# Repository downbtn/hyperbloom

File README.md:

# hyperbloom
great value chipwhisperer

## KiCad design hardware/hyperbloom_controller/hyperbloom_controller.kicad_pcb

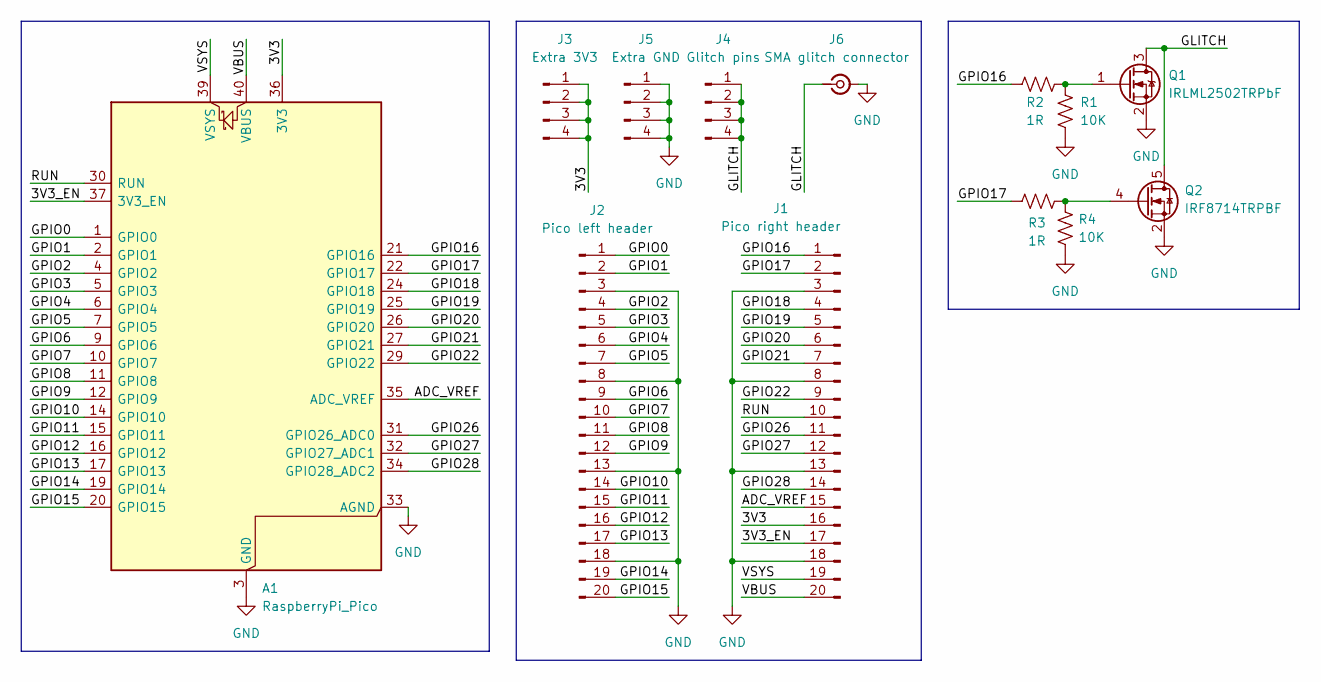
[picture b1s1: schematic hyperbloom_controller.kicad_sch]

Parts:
A1: RaspberryPi_Pico; RaspberryPi_Pico_Common_Unspecified
J1: Pico right header; PinHeader_1x20_P2.54mm_Vertical
J2: Pico left header; PinHeader_1x20_P2.54mm_Vertical
J3: Extra 3V3; PinHeader_1x04_P2.54mm_Vertical
J4: Glitch pins; PinHeader_1x04_P2.54mm_Vertical
J5: Extra GND; PinHeader_1x04_P2.54mm_Vertical
J6: SMA glitch connector; SMA_Amphenol_901-144_Vertical
Q1: IRLML2502TRPbF; SOT-23
Q2: IRF8714TRPBF; SOIC-8_3.9x4.9mm_P1.27mm
R1, R4: 10K; R_0805_2012Metric_Pad1.20x1.40mm_HandSolder
R2, R3: 1R; R_0805_2012Metric_Pad1.20x1.40mm_HandSolder

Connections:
/3V3: A1.36 (3V3), J1.16, J3.1, J3.2, J3.3, J3.4
/3V3_EN: A1.37 (3V3_EN), J1.17
/ADC_VREF: A1.35 (ADC_VREF), J1.15
/GLITCH: J4.1, J4.2, J4.3, J4.4, J6.1 (In), Q1.3 (D), Q2.5 (D), Q2.6 (D), Q2.7 (D), Q2.8 (D)
/GPIO0: A1.1 (GPIO0), J2.1
/GPIO1: A1.2 (GPIO1), J2.2
/GPIO2: A1.4 (GPIO2), J2.4
/GPIO3: A1.5 (GPIO3), J2.5
/GPIO4: A1.6 (GPIO4), J2.6
/GPIO5: A1.7 (GPIO5), J2.7
/GPIO6: A1.9 (GPIO6), J2.9
/GPIO7: A1.10 (GPIO7), J2.10
/GPIO8: A1.11 (GPIO8), J2.11
/GPIO9: A1.12 (GPIO9), J2.12
/GPIO10: A1.14 (GPIO10), J2.14
/GPIO11: A1.15 (GPIO11), J2.15
/GPIO12: A1.16 (GPIO12), J2.16
/GPIO13: A1.17 (GPIO13), J2.17
/GPIO14: A1.19 (GPIO14), J2.19
/GPIO15: A1.20 (GPIO15), J2.20
/GPIO16: A1.21 (GPIO16), J1.1, R2.1
/GPIO17: A1.22 (GPIO17), J1.2, R3.1
/GPIO18: A1.24 (GPIO18), J1.4
/GPIO19: A1.25 (GPIO19), J1.5
/GPIO20: A1.26 (GPIO20), J1.6
/GPIO21: A1.27 (GPIO21), J1.7
/GPIO22: A1.29 (GPIO22), J1.9
/GPIO26: A1.31 (GPIO26_ADC0), J1.11
/GPIO27: A1.32 (GPIO27_ADC1), J1.12
/GPIO28: A1.34 (GPIO28_ADC2), J1.14
/RUN: A1.30 (RUN), J1.10
/VBUS: A1.40 (VBUS), J1.20
/VSYS: A1.39 (VSYS), J1.19
GND: A1.3 (GND), A1.8 (GND), A1.13 (GND), A1.18 (GND), A1.23 (GND), A1.28 (GND), A1.33 (AGND), A1.38 (GND), J1.3, J1.8, J1.13, J1.18, J2.3, J2.8, J2.13, J2.18, J5.1, J5.2, J5.3, J5.4, J6.2 (Ext), Q1.2 (S), Q2.1 (S), Q2.2 (S), Q2.3 (S), R1.2, R4.2
unnamed: Q1.1 (G), R1.1, R2.2
unnamed: Q2.4 (G), R3.2, R4.1

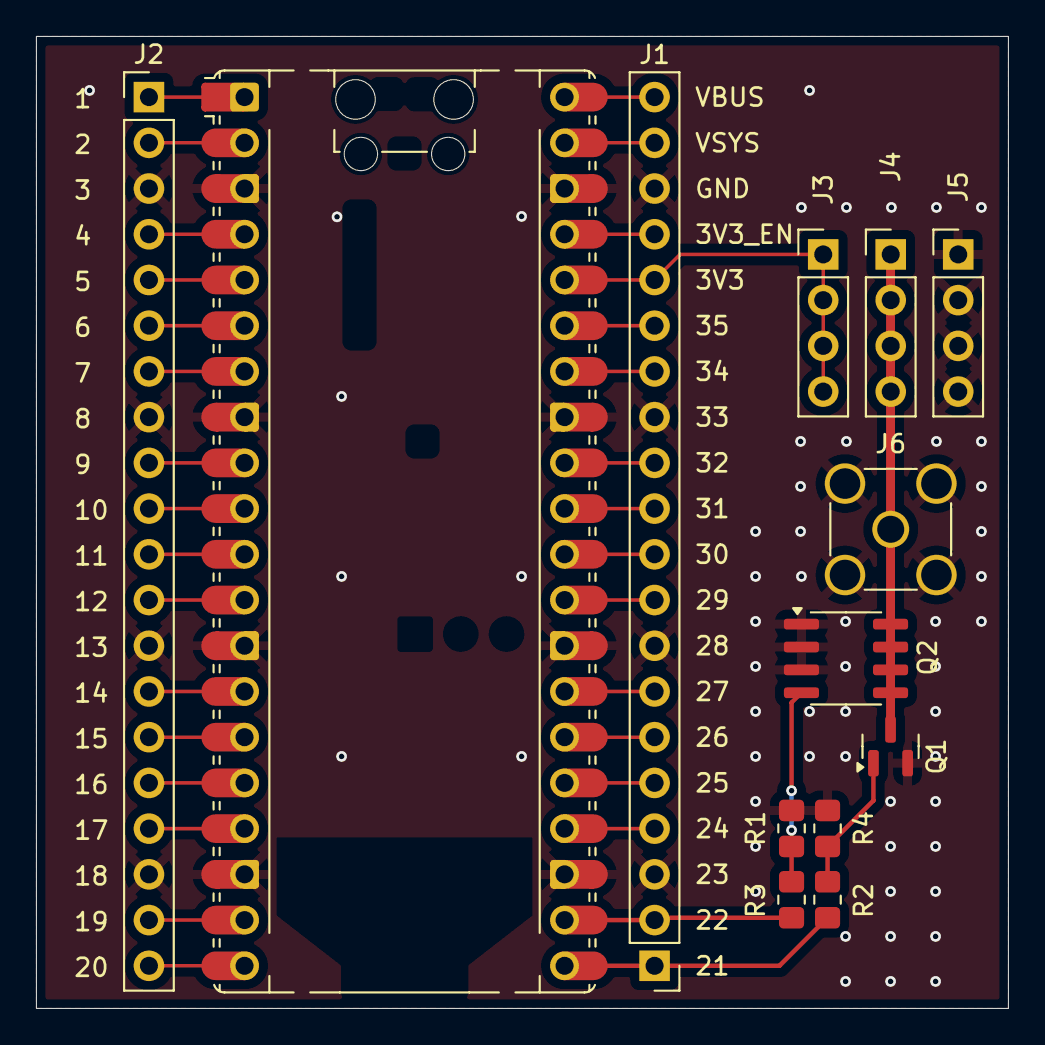
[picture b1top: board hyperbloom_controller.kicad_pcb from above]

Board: 2 copper layers, 54.0 x 54.0 mm, 13 parts (0 on the bottom side), 36 nets.

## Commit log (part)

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2025-05-16 Import 2025 MITRE eCTF insecure example as target
2025-06-21 [target/build] Vendor MSDK for max78000 firmware
    The Oct 2024 version of the MSDK has been vendored into the repo. Various large
    and unnecessary parts of the MSDK like the examples have been rremoved.
2025-06-21 [target/build] Clean up Dockerfile
    - Use Alpine for speed
    - Pin as many versions as possible
2025-06-21 [target] remove crypto example and boot flag
2025-06-25 [target/build] Generate global secrets and include secrets in firmware
    - Global secrets generates root key for channels, subscription key, and
    channel 0 key. Channel keys will be derived by hashing root key ||
    channel #
    - A header file is generated during build containing global secrets so
    that they are accessible to the firmware, channel root key is not
    distributed.
2025-06-25 [target] Remove simple crypto example (again)
2025-06-25 [target] vendor wolfssl 5.8.0
2025-06-27 [target] add buffer size check to uart read
2025-07-07 [target] minimal crypto design
    - derive channel key based on hashing secret root key
    - encrypt subscriptions & frames with AES-CTR
    - authenticate all metadata and ciphertext (vulnerable to timing)
2025-07-09 [target] clang-format
2025-07-09 [target] add pycryptodome to design pyproject
2025-07-17 [controller] add glitch controller pcb kicad files
    The design is subject to change as the layout is kinda bad and I haven't
    finished assembling it irl to test yet.
